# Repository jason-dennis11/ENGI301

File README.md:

# ENGI301
Repository for all ENGI301 course work 

assignment_05:
  
    simple_calc.py - file that runs a program for a simple calculator 
  
    blink_USR3.py - file that runs a program to blink the USR3 LED on the PocketBeagle board at 5 Hz
  
project_1:

    Contains files related to project 1
    
project_2: 

    Contains files related to project 2

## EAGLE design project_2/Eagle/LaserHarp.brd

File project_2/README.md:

#  Laser Harp Controller PCB
  A PCB design for a laser harp using 5V laser diodes and a PocketBeagle. Play musical notes just by waving your hand!

Docs - contains project proposal, Bill-of-Materials.csv, and a pdf of the schematics

Eagle - contains library, schematics, and layout files for PCB design 

MFG - contains manufacturing files 

## Hackster Page 
https://www.hackster.io/308238/laser-harp-controller-7187ea

## Motivation 
Do you know how to play an instrument? Well, I sure do not. Since I was in middle school, I always wanted to learn how to play an instrument and how to read music. Music theory was something I Unfortunately, I never got the opportunity to do so. As a senior in college, I decided it’s time for that to change. I combined my interest in music and my love for electronics into a Laser Harp Controller that allows one to play a mixture of the notes in an octave by simply waving their hand between the lasers! I am sharing this PCB with the open source community to allow all to enjoy and maybe even build their own Laser Harp!

## License   
Copyright 2019 Jason Dennis

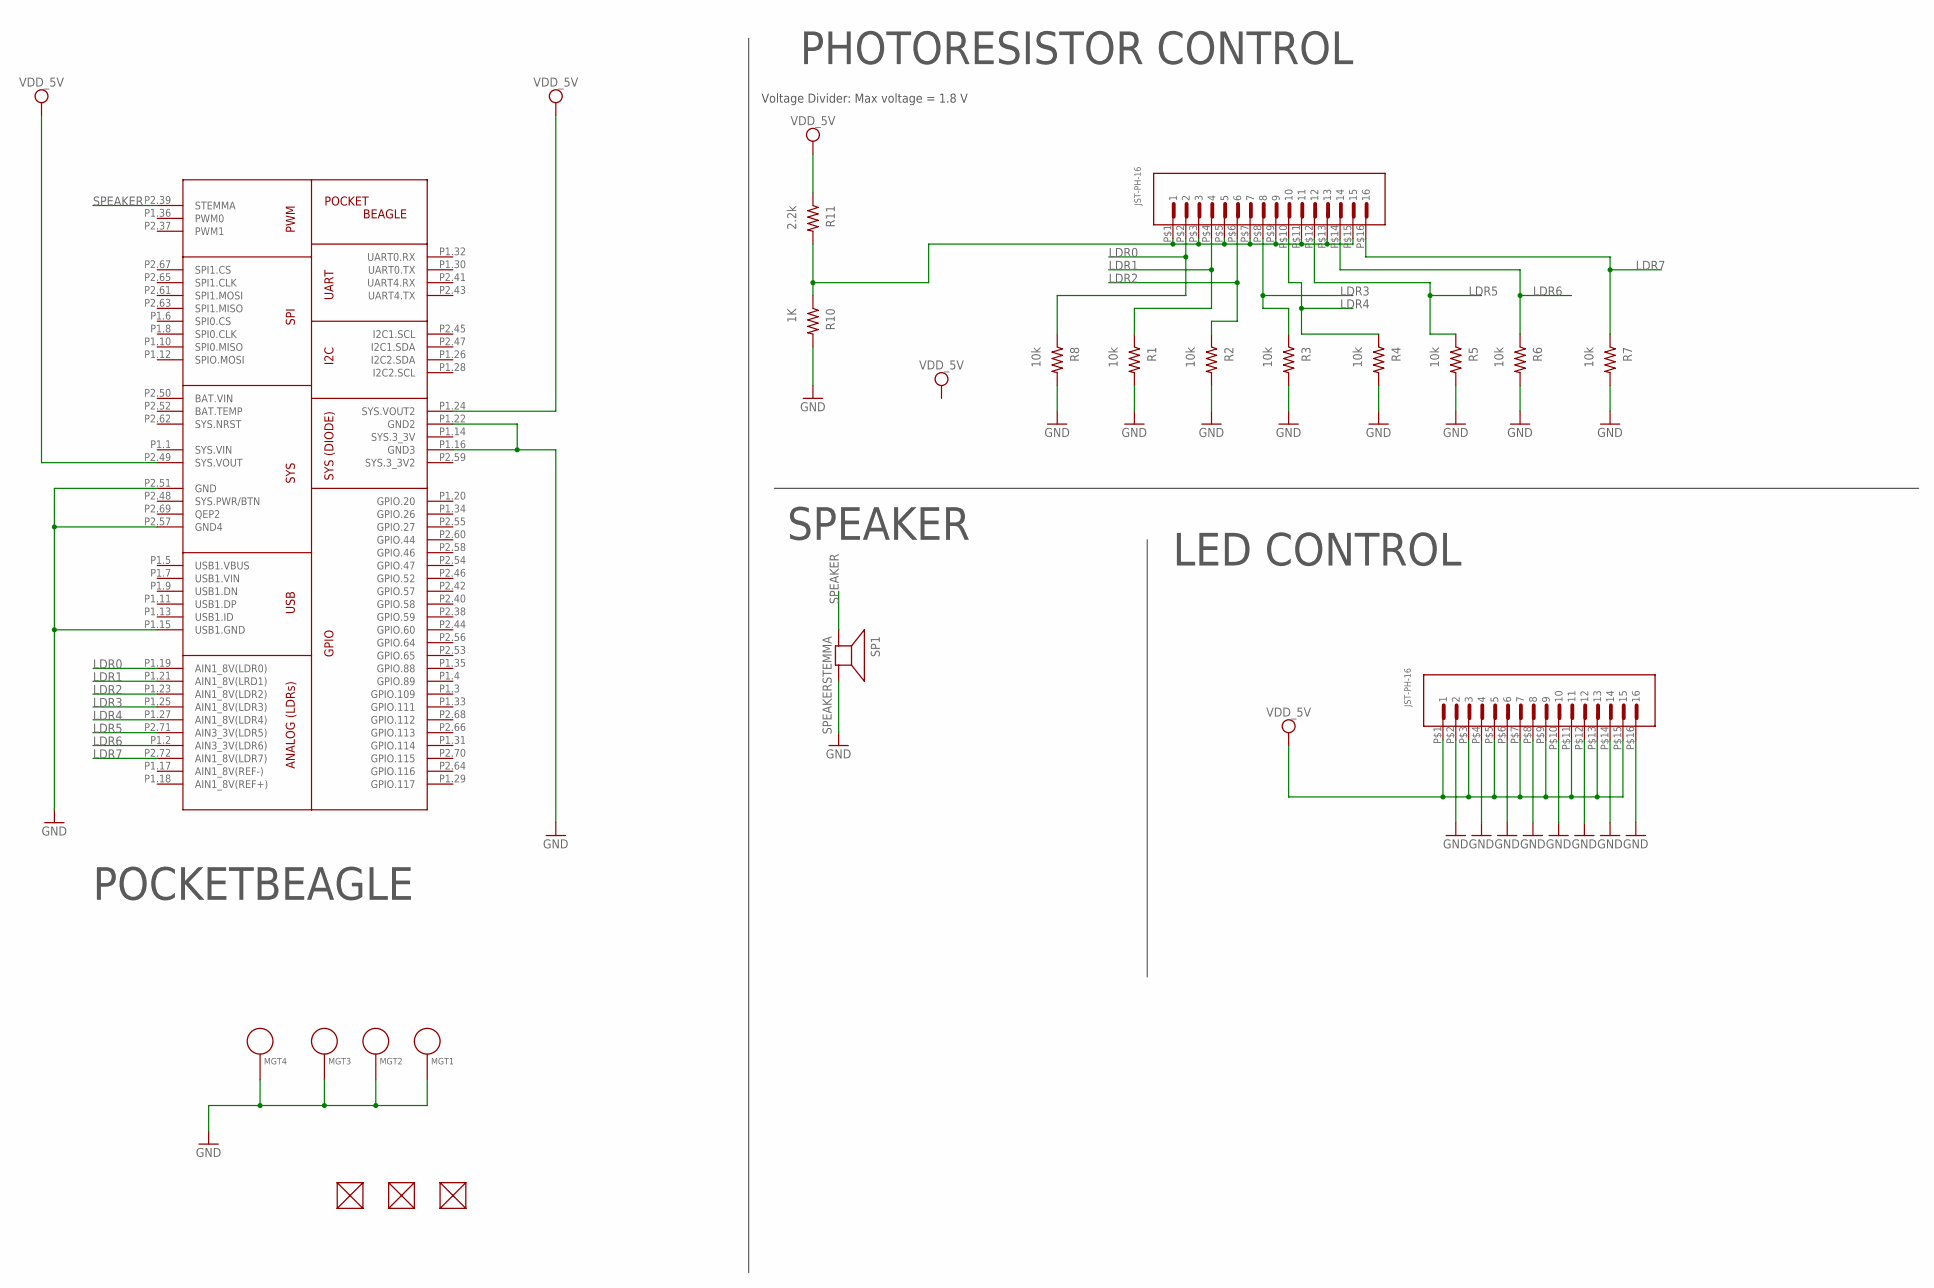
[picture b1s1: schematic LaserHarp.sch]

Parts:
FUD1, FUD2, FUD3: FIDUCIAL; FIDUCIAL_40MIL
MGT1, MGT2, MGT3, MGT4: MOUNTING_HOLE
R1, R2, R3, R4, R5, R6, R7, R8: 10k; R0603
R10: 1K; R0603
R11: 2.2k; R0603
SP1: SPEAKERSTEMMA; STEMMA
U1: POCKETBEAGLE
U$1, U$2: JST-PH-16

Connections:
GND: MGT1.P$1, MGT2.P$1, MGT3.P$1, MGT4.P$1, R1.2, R2.2, R3.2, R4.2, R5.2, R6.2, R7.2, R8.2, R10.2, SP1.P$2 (-), U1.P1.15 (USB1.GND), U1.P1.16 (GND3), U1.P1.22 (GND2), U1.P2.51 (GND), U1.P2.57 (GND4), U$1.P$2 (2), U$1.P$4 (4), U$1.P$6 (6), U$1.P$8 (8), U$1.P$10 (10), U$1.P$12 (12), U$1.P$14 (14), U$1.P$16 (16)
LDR0: R8.1, U1.P1.19 (AIN1_8V(LDR0)), U$2.P$2 (2)
LDR1: R1.1, U1.P1.21 (AIN1_8V(LRD1)), U$2.P$4 (4)
LDR2: R2.1, U1.P1.23 (AIN1_8V(LDR2)), U$2.P$6 (6)
LDR3: R3.1, U1.P1.25 (AIN1_8V(LDR3)), U$2.P$8 (8)
LDR4: R4.1, U1.P1.27 (AIN1_8V(LDR4)), U$2.P$10 (10)
LDR5: R5.1, U1.P2.71 (AIN3_3V(LDR5)), U$2.P$12 (12)
LDR6: R6.1, U1.P1.2 (AIN3_3V(LDR6)), U$2.P$14 (14)
LDR7: R7.1, U1.P2.72 (AIN1_8V(LDR7)), U$2.P$16 (16)
unnamed: R10.1, R11.2, U$2.P$1 (1), U$2.P$3 (3), U$2.P$5 (5), U$2.P$7 (7), U$2.P$9 (9), U$2.P$11 (11), U$2.P$13 (13), U$2.P$15 (15)
SPEAKER: SP1.P$1 (+), U1.P2.39 (STEMMA)
VDD_5V: R11.1, U1.P1.24 (SYS.VOUT2), U1.P2.49 (SYS.VOUT), U$1.P$1 (1), U$1.P$3 (3), U$1.P$5 (5), U$1.P$7 (7), U$1.P$9 (9), U$1.P$11 (11), U$1.P$13 (13), U$1.P$15 (15)

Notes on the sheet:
POCKETBEAGLE
PHOTORESISTOR CONTROL
SPEAKER
LED CONTROL
Voltage Divider: Max voltage = 1.8 V

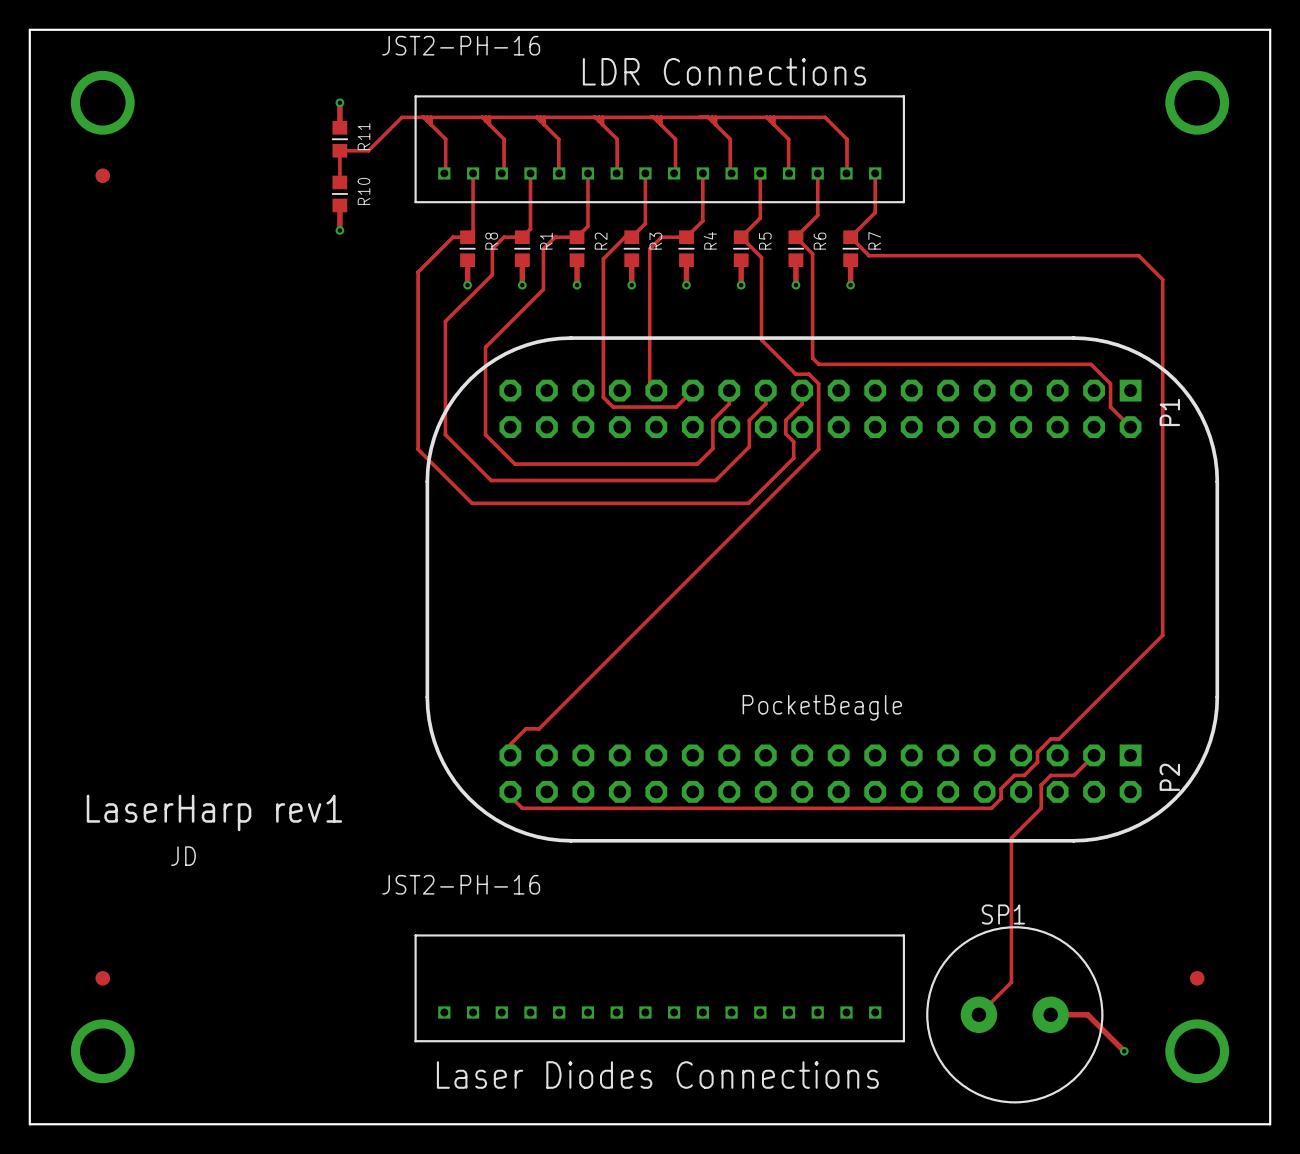
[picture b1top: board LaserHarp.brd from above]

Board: 4 copper layers, 86.4 x 76.2 mm, 21 parts (0 on the bottom side), 12 nets.

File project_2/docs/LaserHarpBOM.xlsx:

Designator | Manufacturer/MPN | Value | Package | Quantity | Description
FUD1-FUD3 | n/a | FIDUCIAL | FIDUCIAL_40MIL | 0 | Fiducials (DNP)
MGT1-MGT4 | n/a | MOUNTING_HOLE | MOUNTING_HOLE | 0 | Chassis Mounting Hole w/GND connection ability
R10 | MF-RES-0603-1K | 1K | R0603 | 1 | Resistor Thick Fil 0603 1K ohm 5% 100mW
R11 | TE Connectivity CRG0603F2K2 | 2.2K | R0603 | 1 | Resistor Thick Fil 0603 2.2K ohm 1% 0.1W
R1-R8 | MF-RES-0603-10K | 10K | R0603 | 8 | Resistor Thick Fil 0603 10K ohm 5% 100mW
SP1 | Adafruit Inudstries 3885 | SPEAKERSTEMMA | STEMMA | 1 | Adafruit STEMMA Speaker - Plug and Play Audio Amplifier
U$1-U$2 | JST B16B-XH-A(LF)SN) | JST-PH-16 | JST-PH-16 | 2 | ShroudedHdr, ThruHole, Top Entry, 16Circuit, 2.5mmPitch
U1 | BeagleBoard POCKETBEAGLE-SC-569 | POCKETBEAGLE | POCKETBEAGLE | 1 | BeagleBoard PocketBeagle - Linux-Enabled USB Keyfob Computer

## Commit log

2019-10-26 commit project introduction
2019-11-19 commit project files to github
2019-11-27 add project_2
